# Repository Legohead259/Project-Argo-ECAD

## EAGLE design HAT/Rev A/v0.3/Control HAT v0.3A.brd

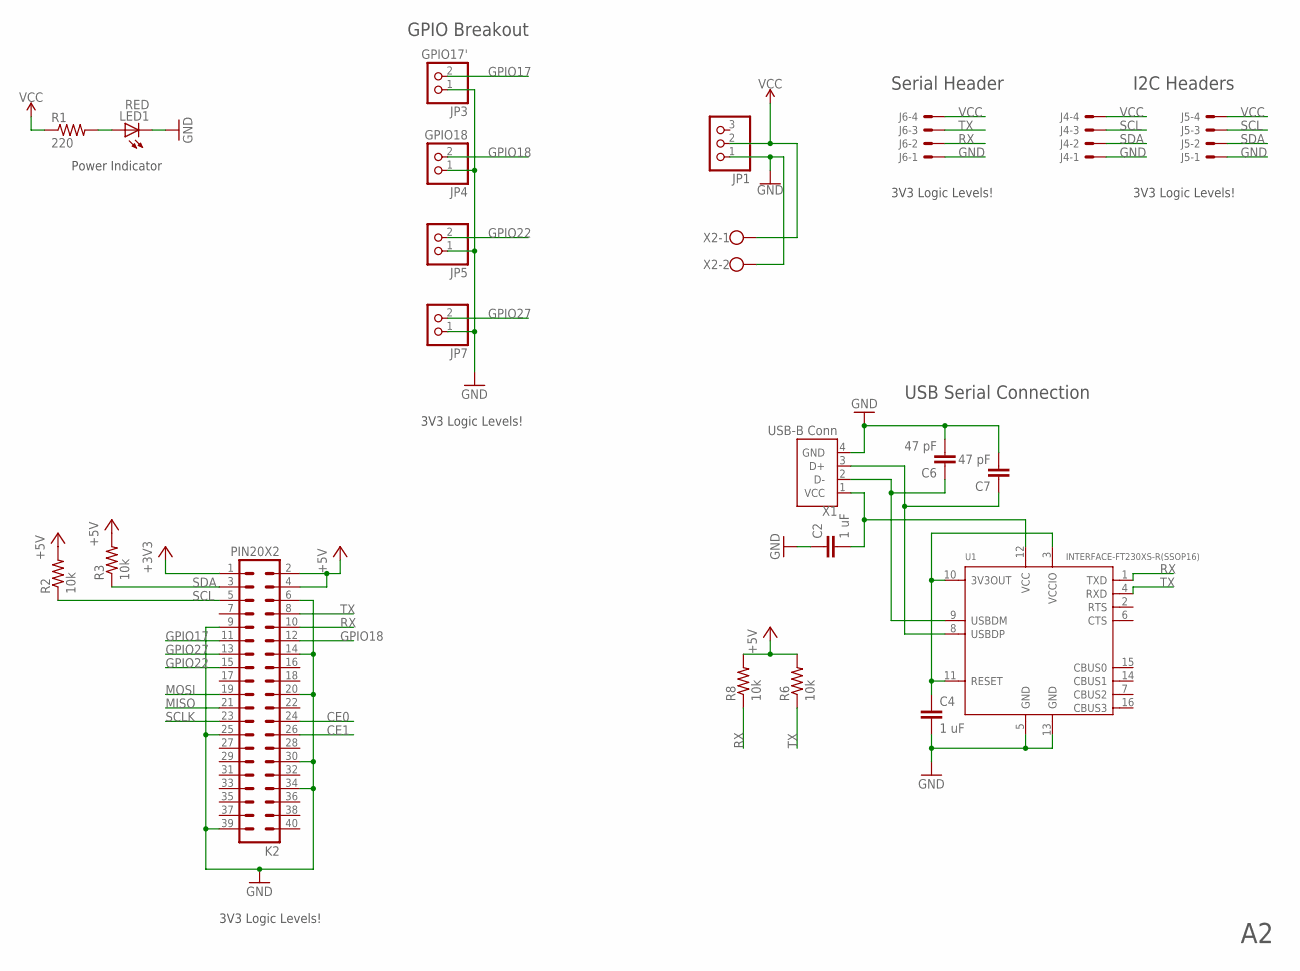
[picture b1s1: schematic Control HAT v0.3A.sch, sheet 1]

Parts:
C2, C4: 1 uF; C0603
C6, C7: 47 pF; C0603
J4, J5, J6: JST-XH-04-PIN-LONG-PAD; JST-XH-04-PACKAGE-LONG-PAD
JP1: PINHD-1X3; 1X03
JP3: GPIO17'; 1X02
JP4: GPIO18; 1X02
JP5, JP7: PINHD-1X2; 1X02
K2: PIN20X2; PIN_20X2
LED1: RED; CHIP-LED0603
R1: 220; M1206
R2, R3, R6, R8: 10k; M1206
U1: INTERFACE-FT230XS-R(SSOP16); SSOP16-0.635-5X4MM
X1: USB-B Conn; OST_USB-B1HSB6
X2: W237-102

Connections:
3V3OUT: C4.1, U1.3 (VCCIO), U1.10 (3V3OUT), U1.11 (RESET)
+3V3: K2.1
+5V: K2.2, K2.4, R2.2, R3.2, R6.2, R8.2
CE0: K2.24
CE1: K2.26
GND: C2.1, C4.2, C6.2, C7.2, J4.1, J5.1, J6.1, JP1.1, JP3.1, JP4.1, JP5.1, JP7.1, K2.6, K2.9, K2.14, K2.20, K2.25, K2.30, K2.34, K2.39, LED1.C, U1.5 (GND), U1.13 (GND), X1.4 (GND), X2.2; also elsewhere on the board
GPIO17: JP3.2, K2.11
GPIO18: JP4.2, K2.12
GPIO22: JP5.2, K2.15
GPIO27: JP7.2, K2.13
MISO: K2.21
MOSI: K2.19
unnamed: C6.1, U1.9 (USBDM), X1.2 (D-)
unnamed: LED1.A, R1.2
unnamed: C2.2, U1.12 (VCC), X1.1 (VCC)
unnamed: C7.1, U1.8 (USBDP), X1.3 (D+)
RX: J6.2, K2.10, R8.1, U1.1 (TXD)
SCL: J4.3, J5.3, K2.5, R2.1; also elsewhere on the board
SCLK: K2.23
SDA: J4.2, J5.2, K2.3, R3.1; also elsewhere on the board
TX: J6.3, K2.8, R6.1, U1.4 (RXD)
VCC: J4.4, J5.4, J6.4, JP1.2, R1.1, X2.1; also elsewhere on the board

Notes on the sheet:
I2C Headers
3V3 Logic Levels!
USB Serial Connection
Serial Header
Power Indicator
GPIO Breakout

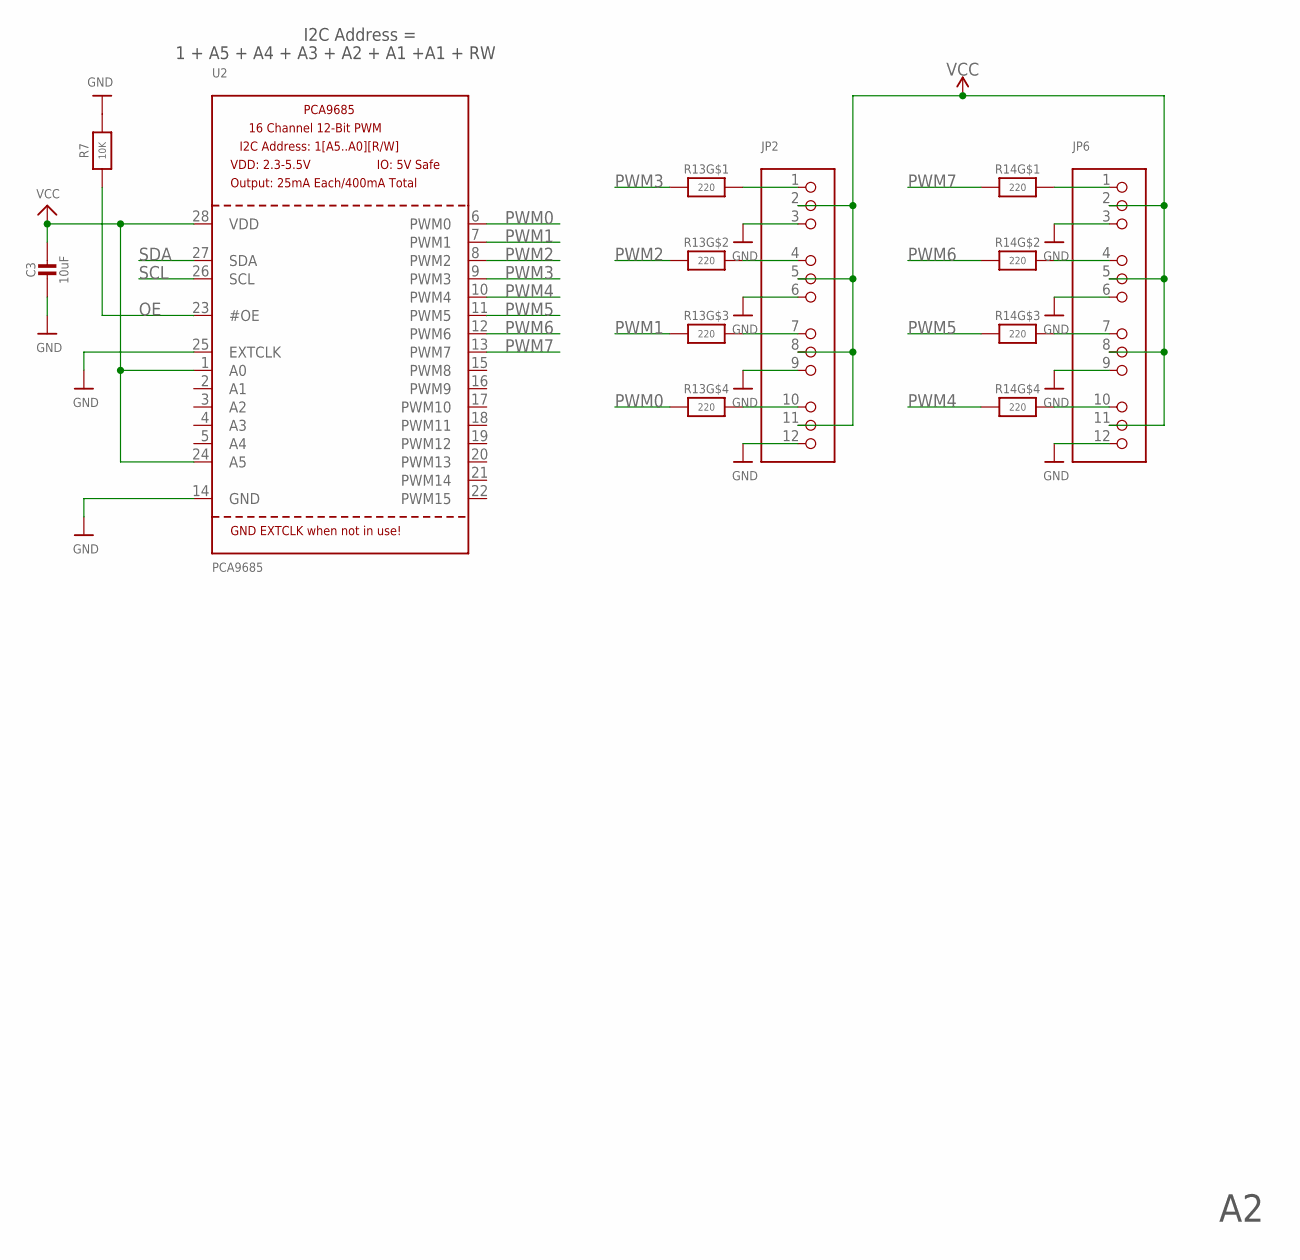
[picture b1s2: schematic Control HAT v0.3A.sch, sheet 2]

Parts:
C3: 10uF; 0805-NO
JP2, JP6: HEADER-3X04; 3X04
R7: 10K; 0805-NO
R13, R14: 220; RESPACK_4X0603
U2: PCA9685; TSSOP28

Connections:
GND: C3.2, JP2.3, JP2.6, JP2.9, JP2.12, JP6.3, JP6.6, JP6.9, JP6.12, R7.2, U2.14 (GND), U2.25 (EXTCLK); also elsewhere on the board
unnamed: JP2.1, R13.8 (2)
unnamed: JP2.4, R13.7 (2)
unnamed: JP2.7, R13.6 (2)
unnamed: JP2.10, R13.5 (2)
unnamed: JP6.10, R14.5 (2)
unnamed: JP6.7, R14.6 (2)
unnamed: JP6.4, R14.7 (2)
unnamed: JP6.1, R14.8 (2)
OE: R7.1, U2.23 (#OE)
PWM0: R13.4 (1), U2.6 (PWM0)
PWM1: R13.3 (1), U2.7 (PWM1)
PWM2: R13.2 (1), U2.8 (PWM2)
PWM3: R13.1, U2.9 (PWM3)
PWM4: R14.4 (1), U2.10 (PWM4)
PWM5: R14.3 (1), U2.11 (PWM5)
PWM6: R14.2 (1), U2.12 (PWM6)
PWM7: R14.1, U2.13 (PWM7)
SCL: U2.26 (SCL); also elsewhere on the board
SDA: U2.27 (SDA); also elsewhere on the board
VCC: C3.1, JP2.2, JP2.5, JP2.8, JP2.11, JP6.2, JP6.5, JP6.8, JP6.11, U2.1 (A0), U2.24 (A5), U2.28 (VDD); also elsewhere on the board

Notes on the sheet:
1 + A5 + A4 + A3 + A2 + A1 +A1 + RW
I2C Address =

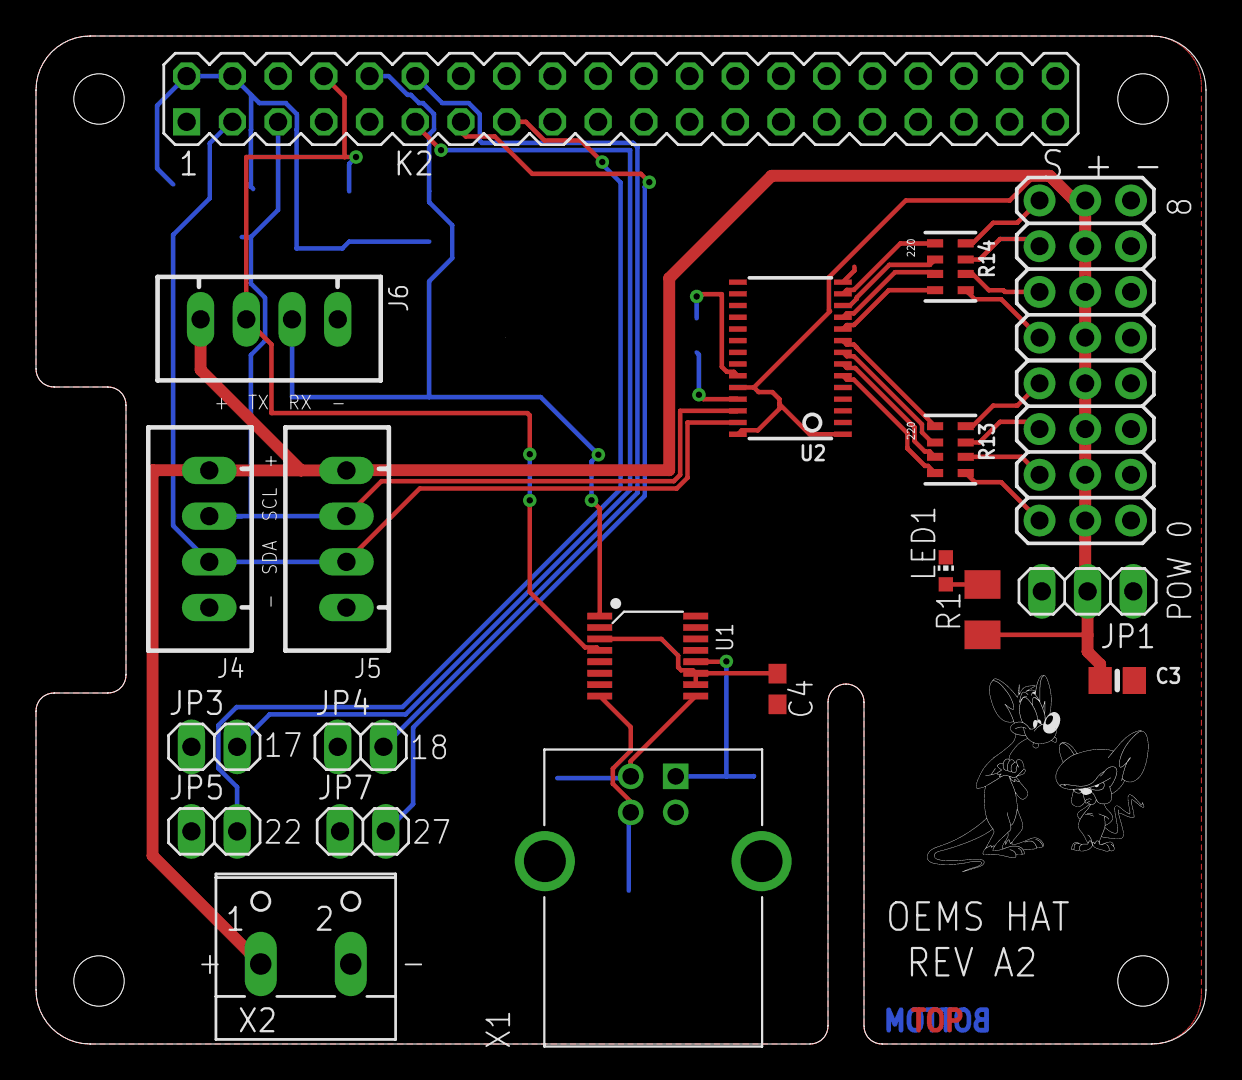
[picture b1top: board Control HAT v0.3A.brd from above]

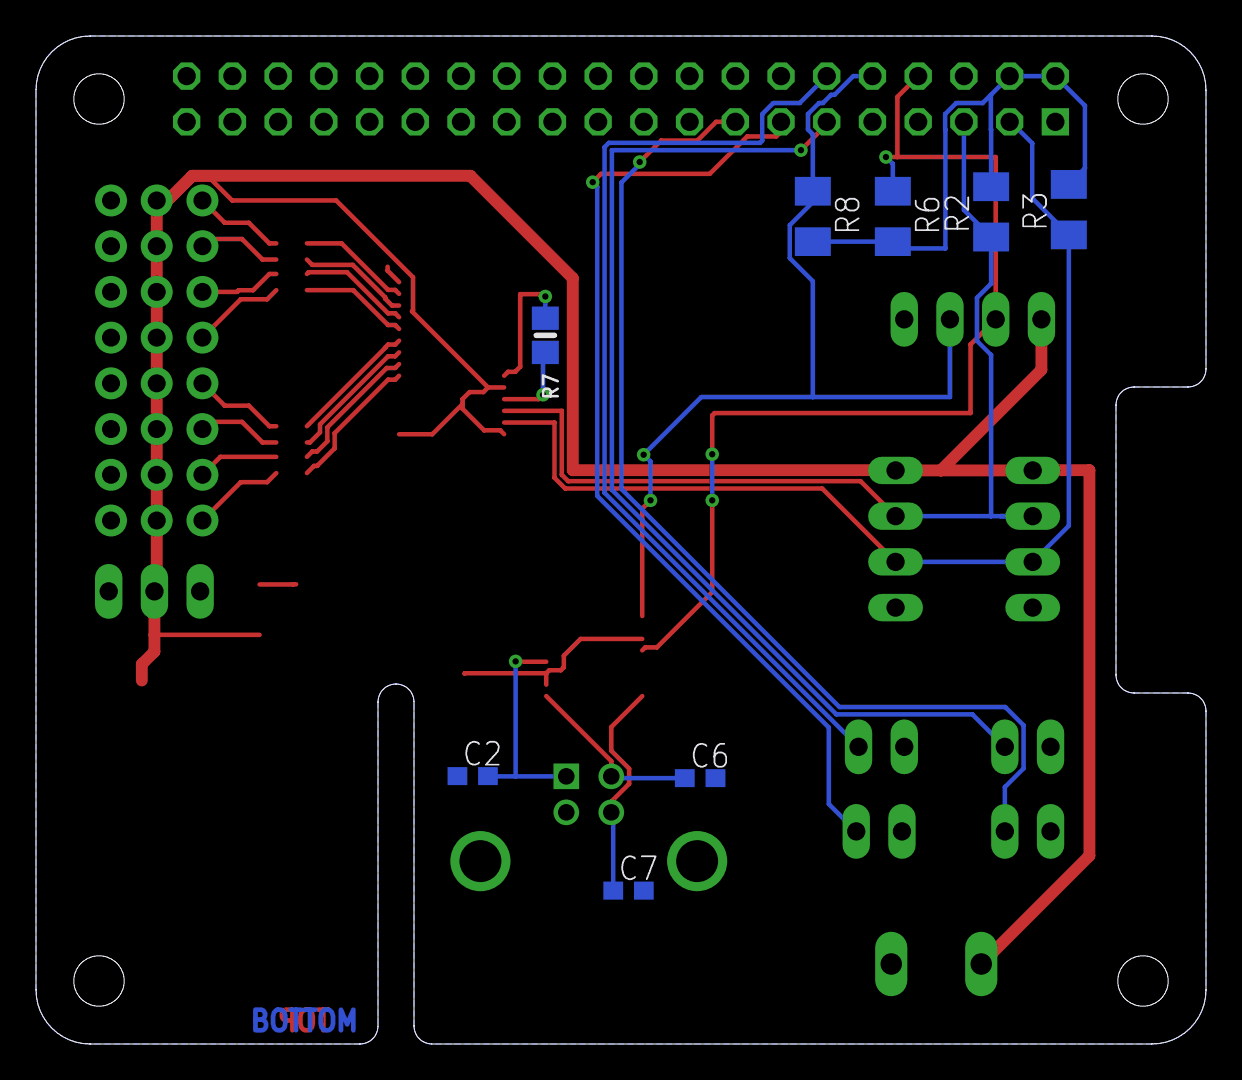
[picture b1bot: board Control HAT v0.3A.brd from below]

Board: 2 copper layers, 65.0 x 56.0 mm, 29 parts (8 on the bottom side), 33 nets.

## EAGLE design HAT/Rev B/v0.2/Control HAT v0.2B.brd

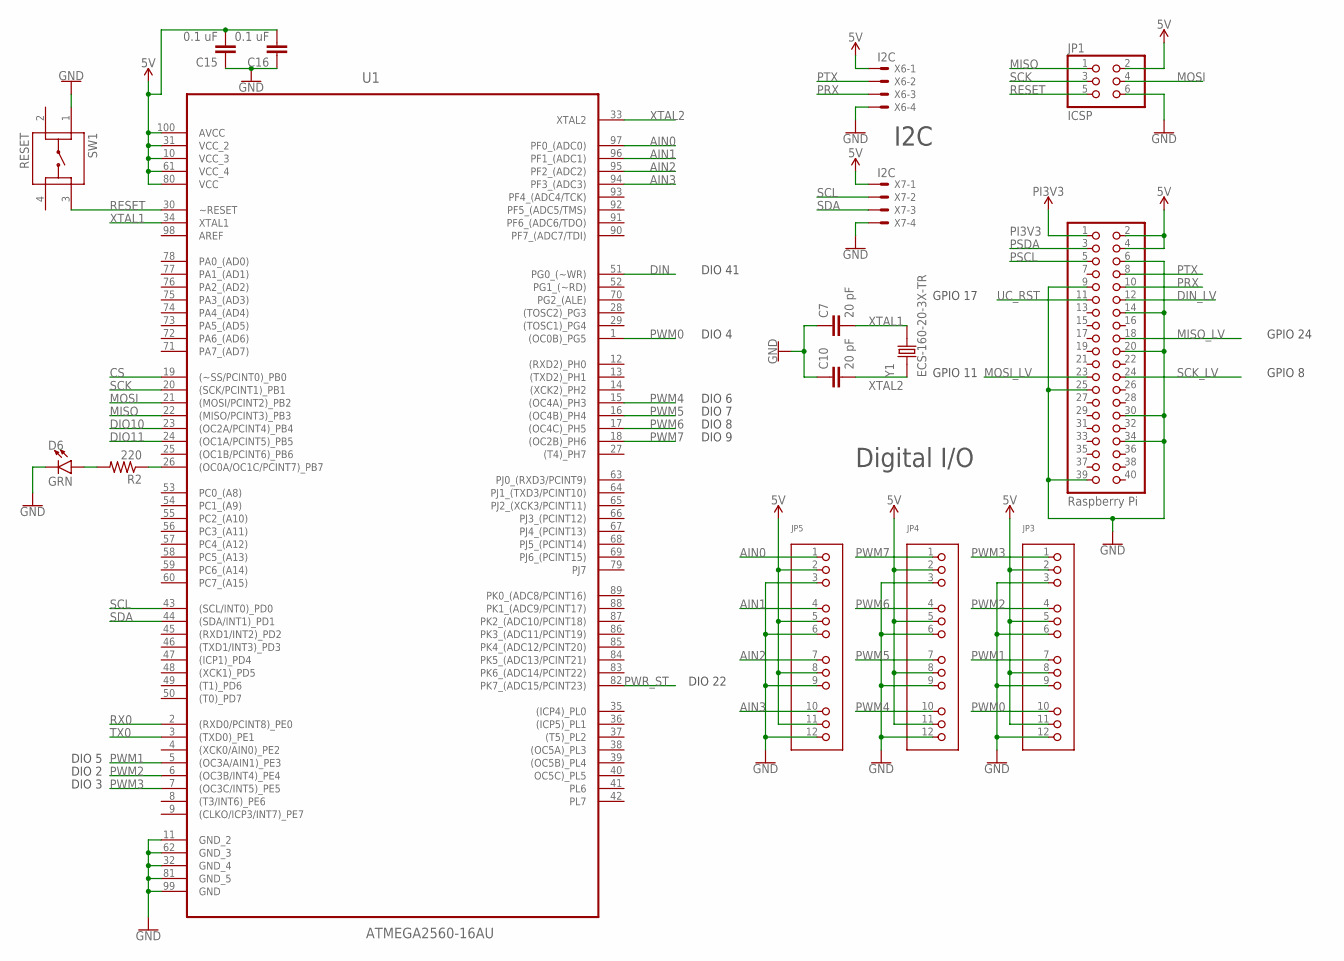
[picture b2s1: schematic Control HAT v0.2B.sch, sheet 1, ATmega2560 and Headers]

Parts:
C7, C10: 20 pF; C0603
C15, C16: 0.1 uF; C0603
D6: GRN; LED-0603
JP1: ICSP; 2X03
JP2: Raspberry Pi; 2X20
JP3, JP4, JP5: HEADER-3X04; 3X04
R2: 220; R0603
SW1: RESET; SW_1825910-6-4
U1: ATMEGA2560-16AU; QFP50P1600X1600X120-100N
X6, X7: I2C; JST-XH-04-PACKAGE-LONG-PAD
Y1: ECS-160-20-3X-TR; XTAL_ECS-160-20-3X-TR

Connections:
5V: C15.2, C16.2, JP1.2, JP2.2, JP2.4, JP3.2, JP3.5, JP3.8, JP3.11, JP4.2, JP4.5, JP4.8, JP4.11, JP5.2, JP5.5, JP5.8, JP5.11, U1.10 (VCC_3), U1.31 (VCC_2), U1.61 (VCC_4), U1.80 (VCC), U1.100 (AVCC), X6.1, X7.1; also elsewhere on the board
AIN0: JP5.1, U1.97 (PF0_(ADC0))
AIN1: JP5.4, U1.96 (PF1_(ADC1))
AIN2: JP5.7, U1.95 (PF2_(ADC2))
AIN3: JP5.10, U1.94 (PF3_(ADC3))
CS: U1.19 ((~SS/PCINT0)_PB0); also elsewhere on the board
DIN: U1.51 (PG0_(~WR)); also elsewhere on the board
DIN_LV: JP2.12; also elsewhere on the board
DIO10: U1.23 ((OC2A/PCINT4)_PB4)
DIO11: U1.24 ((OC1A/PCINT5)_PB5)
DIO13: R2.1, U1.26 ((OC0A/OC1C/PCINT7)_PB7)
GND: C7.1, C10.1, C15.1, C16.1, D6.C, JP1.6, JP2.6, JP2.9, JP2.14, JP2.20, JP2.25, JP2.30, JP2.34, JP2.39, JP3.3, JP3.6, JP3.9, JP3.12, JP4.3, JP4.6, JP4.9, JP4.12, JP5.3, JP5.6, JP5.9, JP5.12, SW1.1, U1.11 (GND_2), U1.32 (GND_4), U1.62 (GND_3), U1.81 (GND_5), U1.99 (GND), X6.4, X7.4; also elsewhere on the board
MISO: JP1.1, U1.22 ((MISO/PCINT3)_PB3); also elsewhere on the board
MISO_LV: JP2.18; also elsewhere on the board
MOSI: JP1.4, U1.21 ((MOSI/PCINT2)_PB2); also elsewhere on the board
MOSI_LV: JP2.23; also elsewhere on the board
unnamed: D6.A, R2.2
PI3V3: JP2.1; also elsewhere on the board
PRX: JP2.10, X6.3
PSCL: JP2.5; also elsewhere on the board
PSDA: JP2.3; also elsewhere on the board
PTX: JP2.8, X6.2
PWM0: JP3.10, U1.1 ((OC0B)_PG5)
PWM1: JP3.7, U1.5 ((OC3A/AIN1)_PE3)
PWM2: JP3.4, U1.6 ((OC3B/INT4)_PE4)
PWM3: JP3.1, U1.7 ((OC3C/INT5)_PE5)
PWM4: JP4.10, U1.15 ((OC4A)_PH3)
PWM5: JP4.7, U1.16 ((OC4B)_PH4)
PWM6: JP4.4, U1.17 ((OC4C)_PH5)
PWM7: JP4.1, U1.18 ((OC2B)_PH6)
PWR_ST: U1.82 (PK7_(ADC15/PCINT23)); also elsewhere on the board
RESET: JP1.5, SW1.3, U1.30 (~RESET); also elsewhere on the board
RX0: U1.2 ((RXD0/PCINT8)_PE0); also elsewhere on the board
SCK: JP1.3, U1.20 ((SCK/PCINT1)_PB1); also elsewhere on the board
SCK_LV: JP2.24; also elsewhere on the board
SCL: U1.43 ((SCL/INT0)_PD0), X7.2; also elsewhere on the board
SDA: U1.44 ((SDA/INT1)_PD1), X7.3; also elsewhere on the board
TX0: U1.3 ((TXD0)_PE1); also elsewhere on the board
UC_RST: JP2.11; also elsewhere on the board
XTAL1: C7.2, U1.34 (XTAL1), Y1.2
XTAL2: C10.2, U1.33 (XTAL2), Y1.1

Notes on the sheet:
DIO 5
DIO 2
DIO 3
DIO 4
DIO 6
DIO 7
DIO 8
DIO 9
Digital I/O
I2C
DIO 41
GPIO 8
GPIO 24
GPIO 11
GPIO 17
DIO 22

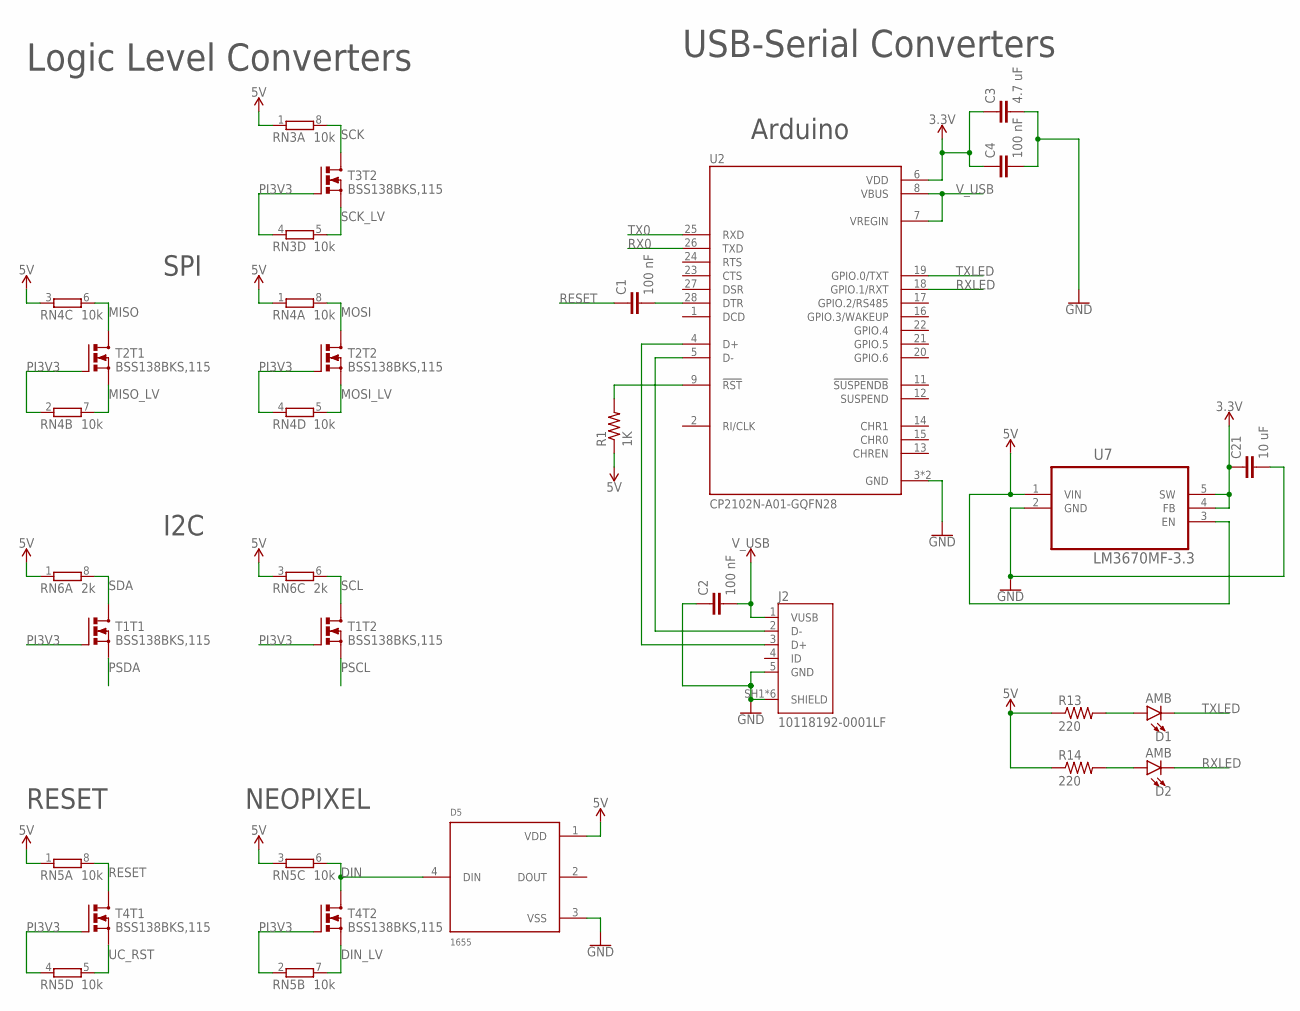
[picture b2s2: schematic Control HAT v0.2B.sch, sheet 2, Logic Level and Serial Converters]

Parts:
C1, C2, C4: 100 nF; C0603
C3: 4.7 uF; C0603
C21: 10 uF; C0603
D1, D2: AMB; LED-0603
D5: 1655; FCI_1655
J2: 10118192-0001LF; AMPHENOL_10118192-0001LF
R1: 1K; R0603
R13, R14: 220; R0603
RN3, RN4, RN5: 10k; EXB28V
RN6: 2k; EXB28V
T1, T2, T3, T4: BSS138BKS,115; SOT363
U2: CP2102N-A01-GQFN28; QFN50P500X500X80-29N
U7: LM3670MF-3.3; SOT95P284X122-5N

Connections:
3.3V: C3.1, C4.1, C21.1, U2.6 (VDD), U7.4 (FB), U7.5 (SW)
5V: D5.1 (VDD), R1.1, R13.1, R14.1, RN3.1, RN4.1, RN4.3 (1), RN5.1, RN5.3 (1), RN6.1, RN6.3 (1), U7.1 (VIN), U7.3 (EN); also elsewhere on the board
DIN: D5.4 (DIN), RN5.6 (2), T4.3 (D); also elsewhere on the board
DIN_LV: RN5.7 (2), T4.4 (S); also elsewhere on the board
GND: C2.1, C3.2, C4.2, C21.2, D5.3 (VSS), J2.5 (GND), J2.SH1 (SHIELD), J2.SH2 (SHIELD), J2.SH3 (SHIELD), J2.SH4 (SHIELD), J2.SH5 (SHIELD), J2.SH6 (SHIELD), U2.3 (GND), U2.29 (GND), U7.2 (GND); also elsewhere on the board
MISO: RN4.6 (2), T2.6 (D); also elsewhere on the board
MISO_LV: RN4.7 (2), T2.1 (S); also elsewhere on the board
MOSI: RN4.8 (2), T2.3 (D); also elsewhere on the board
MOSI_LV: RN4.5 (2), T2.4 (S); also elsewhere on the board
unnamed: J2.2 (D-), U2.5 (D-)
unnamed: J2.3 (D+), U2.4 (D+)
unnamed: R1.2, U2.9 (!RST)
unnamed: D1.A, R13.2
unnamed: D2.A, R14.2
unnamed: C1.2, U2.28 (DTR)
PI3V3: RN3.4 (1), RN4.2 (1), RN4.4 (1), RN5.2 (1), RN5.4 (1), T1.2 (G), T1.5 (G), T2.2 (G), T2.5 (G), T3.5 (G), T4.2 (G), T4.5 (G); also elsewhere on the board
PSCL: T1.4 (S); also elsewhere on the board
PSDA: T1.1 (S); also elsewhere on the board
RESET: C1.1, RN5.8 (2), T4.6 (D); also elsewhere on the board
RX0: U2.26 (TXD); also elsewhere on the board
RXLED: D2.C, U2.18 (GPIO.1/RXT)
SCK: RN3.8 (2), T3.3 (D); also elsewhere on the board
SCK_LV: RN3.5 (2), T3.4 (S); also elsewhere on the board
SCL: RN6.6 (2), T1.3 (D); also elsewhere on the board
SDA: RN6.8 (2), T1.6 (D); also elsewhere on the board
TX0: U2.25 (RXD); also elsewhere on the board
TXLED: D1.C, U2.19 (GPIO.0/TXT)
UC_RST: RN5.5 (2), T4.1 (S); also elsewhere on the board
V_USB: C2.2, J2.1 (VUSB), U2.7 (VREGIN), U2.8 (VBUS)

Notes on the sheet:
Logic Level Converters
I2C
SPI
RESET
NEOPIXEL
USB-Serial Converters
Arduino

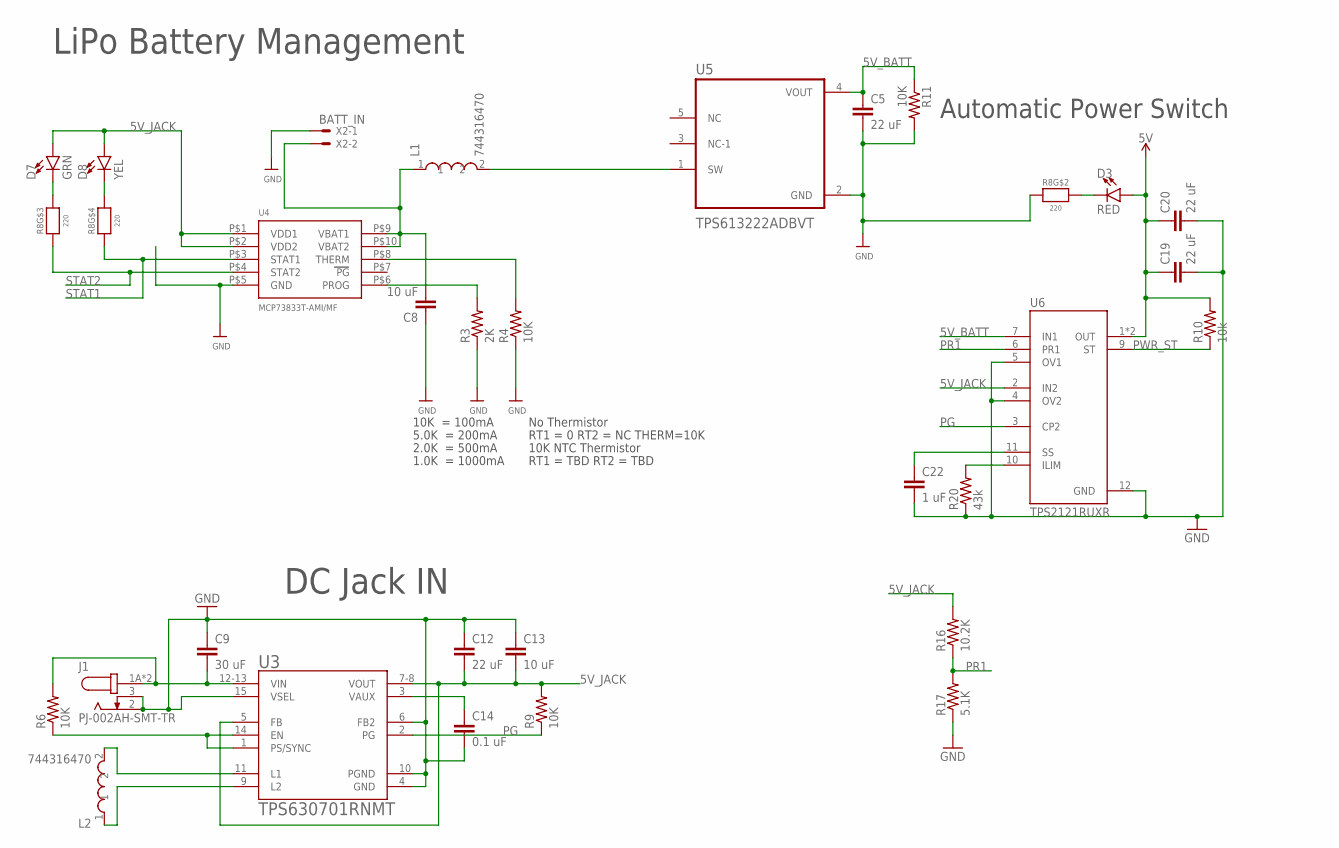
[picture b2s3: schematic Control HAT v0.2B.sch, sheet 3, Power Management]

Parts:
C5, C12, C19, C20: 22 uF; C0603
C8, C13: 10 uF; C0603
C9: 30 uF; C0603
C14: 0.1 uF; C0603
C22: 1 uF; C0603
D3: RED; LED-0603
D7: GRN; LED-0603
D8: YEL; LED-0603
J1: PJ-002AH-SMT-TR; CUI_PJ-002AH-SMT-TR
L1, L2: 744316470; INDC2220X16
R3: 2K; R0603
R4, R6, R9, R11: 10K; R0603
R8: 220; RESPACK_4X0603
R10: 10k; R0603
R16: 10.2K; R0603
R17: 5.1K; R0603
R20: 43k; R0603
U3: TPS630701RNMT; QFN50P250X300X100-15N
U4: MCP73833T-AMI/MF; DFN10_3X3MM
U5: TPS613222ADBVT; SOT95P280X145-5N
U6: TPS2121RUXR; IC_TPS2121RUXR
X2: BATT_IN; JST-XH-02-PACKAGE-LONG-PAD

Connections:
5V: C19.1, C20.1, D3.A, R10.2, U6.1 (OUT), U6.8 (OUT); also elsewhere on the board
5V_BATT: C5.1, R11.1, U5.4 (VOUT), U6.7 (IN1)
5V_JACK: C12.2, C13.2, D7.A, D8.A, R9.2, R16.2, U3.5 (FB), U3.7-8 (VOUT), U4.P$1 (VDD1), U4.P$2 (VDD2), U6.2 (IN2)
BATT: C8.2, L1.1, U4.P$9 (VBAT1), U4.P$10 (VBAT2), X2.2
GND: C5.2, C8.1, C9.1, C12.1, C13.1, C14.2, C19.2, C20.2, C22.2, J1.2, J1.3, R3.1, R4.1, R8.2 (1), R11.2, R17.1, R20.1, U3.4 (GND), U3.6 (FB2), U3.10 (PGND), U3.15 (VSEL), U4.P$5 (GND), U5.2 (GND), U6.4 (OV2), U6.5 (OV1), U6.12 (GND), X2.1; also elsewhere on the board
unnamed: D7.C, R8.6 (2)
unnamed: C9.2, J1.1A (1), J1.1B (1), R6.2, U3.12-13 (VIN)
unnamed: D8.C, R8.5 (2)
unnamed: D3.C, R8.7 (2)
unnamed: L2.2, U3.11 (L1)
unnamed: L2.1, U3.9 (L2)
unnamed: C14.1, U3.3 (VAUX)
unnamed: L1.2, U5.1 (SW)
unnamed: R3.2, U4.P$6 (PROG)
unnamed: R6.1, U3.1 (PS/SYNC), U3.14 (EN)
unnamed: R4.2, U4.P$8 (THERM)
unnamed: R20.2, U6.10 (ILIM)
unnamed: C22.1, U6.11 (SS)
PG: R9.1, U3.2 (PG), U6.3 (CP2)
PR1: R16.1, R17.2, U6.6 (PR1)
PWR_ST: R10.1, U6.9 (ST); also elsewhere on the board
STAT1: R8.4 (1), U4.P$3 (STAT1)
STAT2: R8.3 (1), U4.P$4 (STAT2)

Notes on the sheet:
10K = 100mA
5.0K = 200mA
2.0K = 500mA
1.0K = 1000mA
No Thermistor
RT1 = 0 RT2 = NC THERM=10K
10K NTC Thermistor
RT1 = TBD RT2 = TBD
LiPo Battery Management
DC Jack IN
Automatic Power Switch

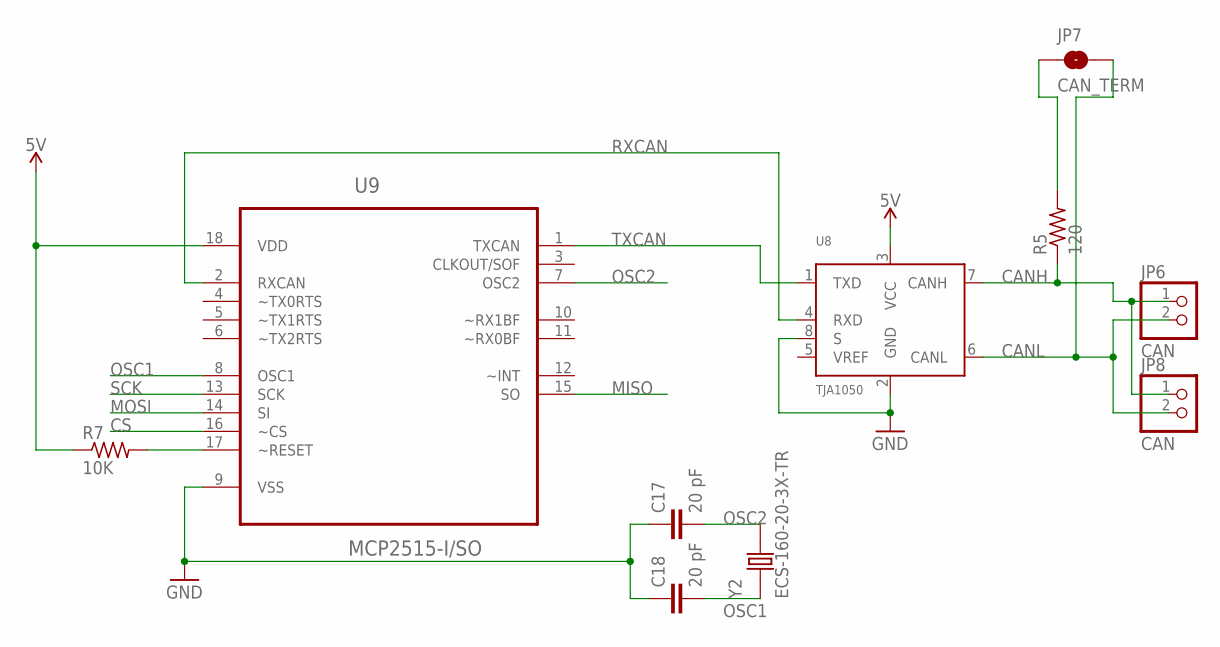
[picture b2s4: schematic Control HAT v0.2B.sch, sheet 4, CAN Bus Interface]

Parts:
C17, C18: 20 pF; C0603
JP6, JP8: CAN; 1X02
JP7: CAN_TERM; SMT-JUMPER_2_NO_NO-SILK
R5: 120; R0603
R7: 10K; R0603
U8: TJA1050; SOT96-1
U9: MCP2515-I/SO; SOIC127P1034X264-18N
Y2: ECS-160-20-3X-TR; XTAL_ECS-160-20-3X-TR

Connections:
5V: R7.1, U8.3 (VCC), U9.18 (VDD); also elsewhere on the board
CANH: JP6.1, JP8.1, R5.1, U8.7 (CANH)
CANL: JP6.2, JP7.2, JP8.2, U8.6 (CANL)
CS: U9.16 (~CS); also elsewhere on the board
GND: C17.1, C18.1, U8.2 (GND), U8.8 (S), U9.9 (VSS); also elsewhere on the board
MISO: U9.15 (SO); also elsewhere on the board
MOSI: U9.14 (SI); also elsewhere on the board
unnamed: JP7.1, R5.2
unnamed: R7.2, U9.17 (~RESET)
OSC1: C18.2, U9.8 (OSC1), Y2.1
OSC2: C17.2, U9.7 (OSC2), Y2.2
RXCAN: U8.4 (RXD), U9.2 (RXCAN)
SCK: U9.13 (SCK); also elsewhere on the board
TXCAN: U8.1 (TXD), U9.1 (TXCAN)

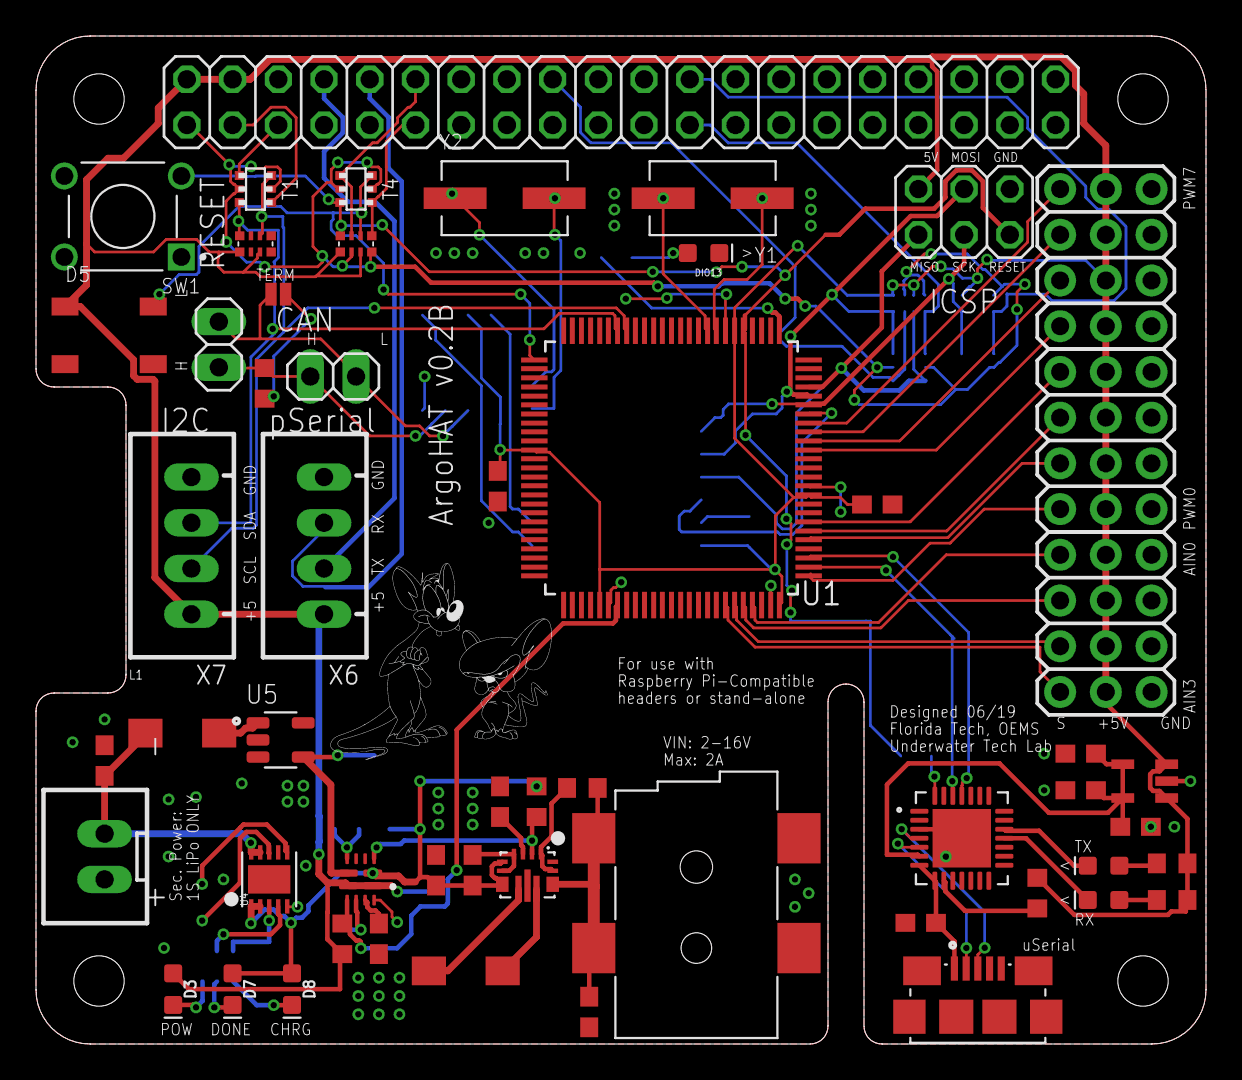
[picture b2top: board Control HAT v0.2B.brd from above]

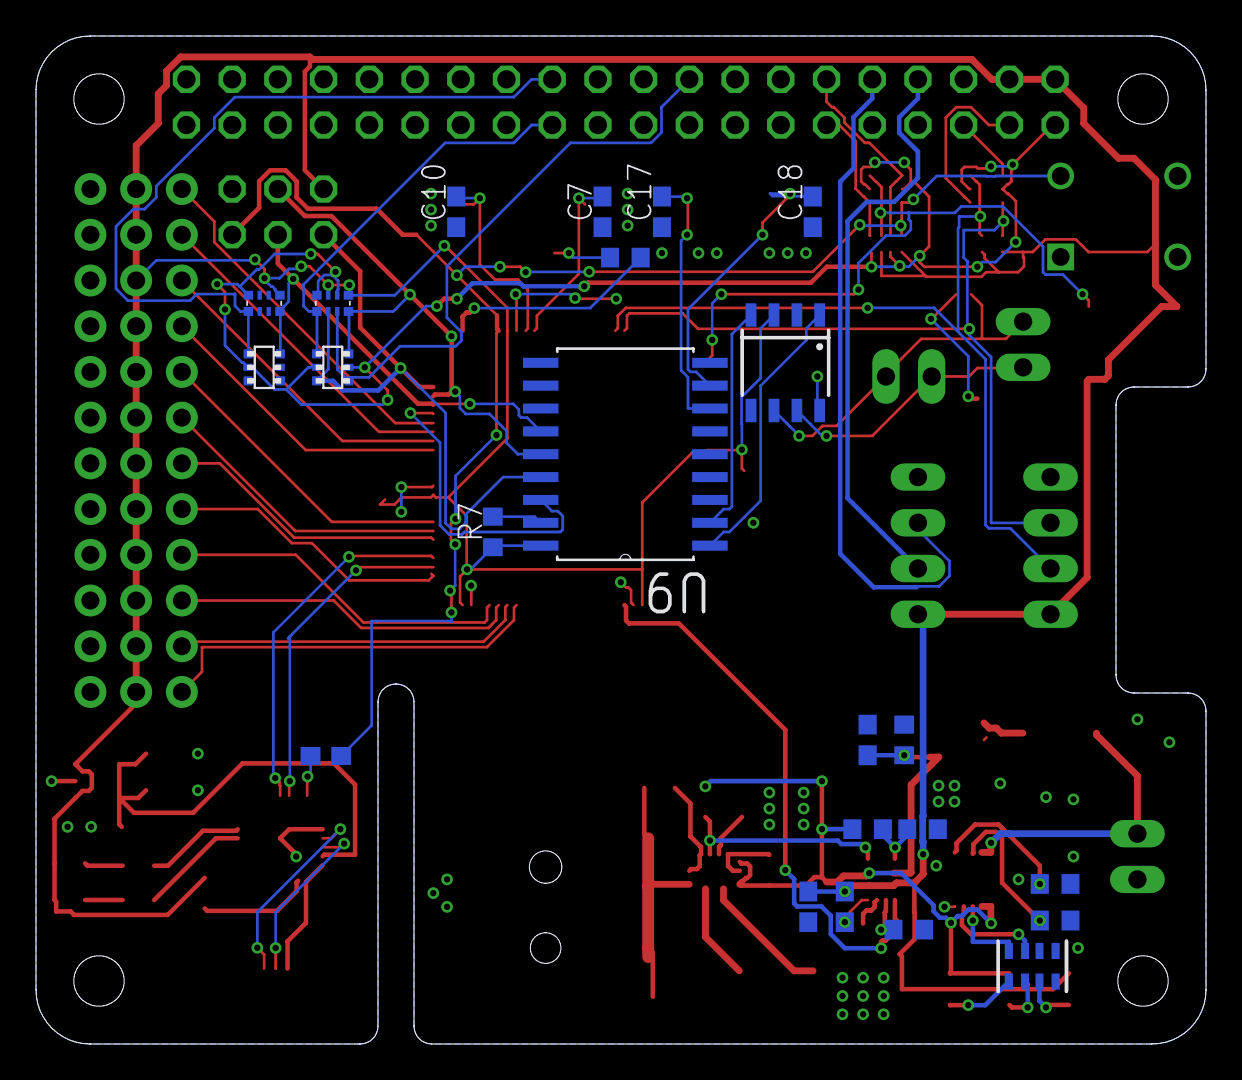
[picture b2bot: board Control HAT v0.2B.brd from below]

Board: 2 copper layers, 65.0 x 56.0 mm, 78 parts (23 on the bottom side), 77 nets.

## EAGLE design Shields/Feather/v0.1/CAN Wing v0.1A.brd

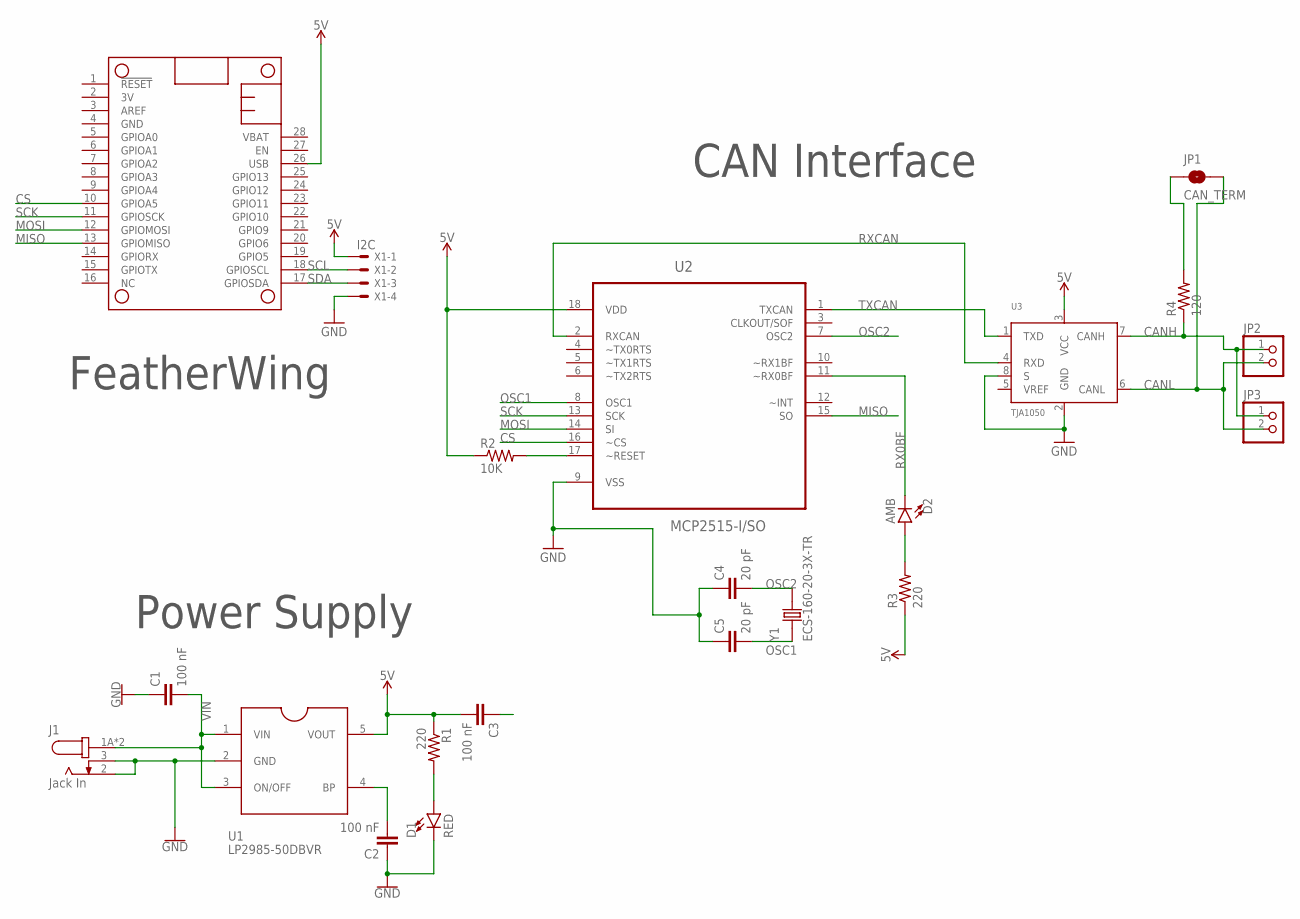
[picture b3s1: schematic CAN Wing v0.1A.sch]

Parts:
C1, C2, C3: 100 nF; C0603
C4, C5: 20 pF; C0603
D1: RED; LED-0603
D2: AMB; LED-0603
J1: Jack In; CUI_PJ-002AH-SMT-TR
JP1: CAN_TERM; SMT-JUMPER_2_NO_NO-SILK
JP2, JP3: PINHD-1X2/90; 1X02/90
MS1: FEATHERWING
R1, R3: 220; R0603
R2: 10K; R0603
R4: 120; R0603
U1: LP2985-50DBVR; SOT23-5
U2: MCP2515-I/SO; SOIC127P1034X264-18N
U3: TJA1050; SOT96-1
X1: I2C; JST-XH-04-PACKAGE-LONG-PAD
Y1: ECS-160-20-3X-TR; XTAL_ECS-160-20-3X-TR

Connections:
5V: C3.2, MS1.26 (USB), R1.1, R2.1, R3.1, U1.5 (VOUT), U2.18 (VDD), U3.3 (VCC), X1.1
CANH: JP2.1, JP3.1, R4.1, U3.7 (CANH)
CANL: JP1.2, JP2.2, JP3.2, U3.6 (CANL)
CS: MS1.10 (GPIOA5), U2.16 (~CS)
GND: C1.1, C2.1, C3.1, C4.1, C5.1, D1.C, J1.2, J1.3, MS1.4 (GND), U1.2 (GND), U2.9 (VSS), U3.2 (GND), U3.8 (S), X1.4
MISO: MS1.13 (GPIOMISO), U2.15 (SO)
MOSI: MS1.12 (GPIOMOSI), U2.14 (SI)
unnamed: JP1.1, R4.2
unnamed: R2.2, U2.17 (~RESET)
unnamed: C2.2, U1.4 (BP)
unnamed: D1.A, R1.2
unnamed: D2.A, R3.2
OSC1: C5.2, U2.8 (OSC1), Y1.1
OSC2: C4.2, U2.7 (OSC2), Y1.2
RX0BF: D2.C, U2.11 (~RX0BF)
RXCAN: U2.2 (RXCAN), U3.4 (RXD)
SCK: MS1.11 (GPIOSCK), U2.13 (SCK)
SCL: MS1.18 (GPIOSCL), X1.2
SDA: MS1.17 (GPIOSDA), X1.3
TXCAN: U2.1 (TXCAN), U3.1 (TXD)
VIN: C1.2, J1.1A (1), J1.1B (1), U1.1 (VIN), U1.3 (ON/OFF)

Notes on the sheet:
Power Supply
CAN Interface
FeatherWing

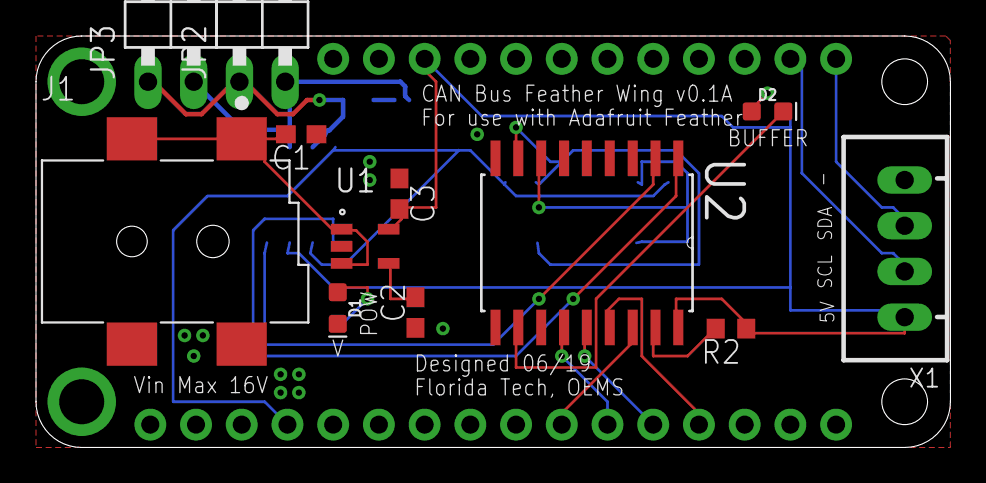
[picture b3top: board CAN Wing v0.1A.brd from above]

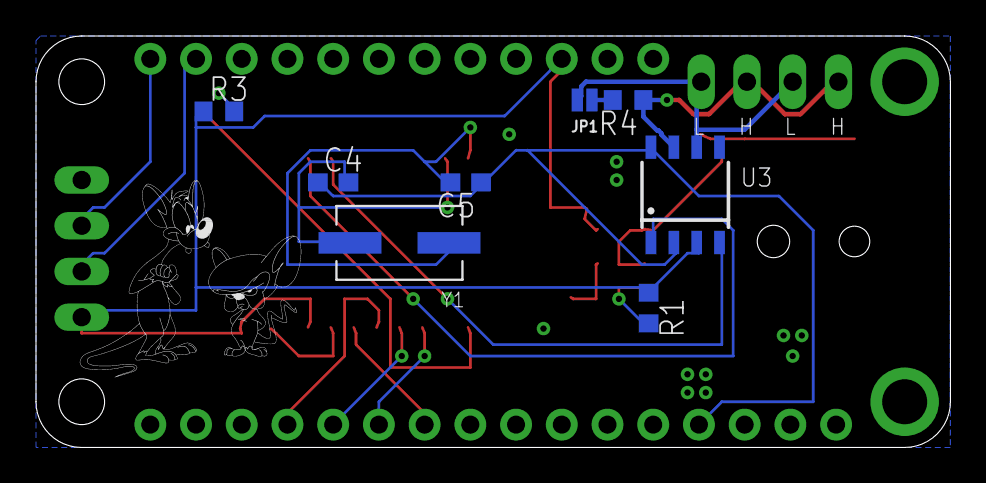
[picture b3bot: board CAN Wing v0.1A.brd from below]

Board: 2 copper layers, 50.8 x 22.9 mm, 21 parts (8 on the bottom side), 21 nets.

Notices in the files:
parts and their libraries:
SparkFun-PowerSymbols: Licensing: Creative Commons ShareAlike 4.0 International - https://creativecommons.org/licenses/by-sa/4.0
